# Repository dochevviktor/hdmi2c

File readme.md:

# HDMI2C Monitor Controller

HDMI2C allows network control (via WiFi) of monitors connected to it via HDMI (via
[DDC]). This allows you to build your own tooling and control systems for your monitors,
rather than relying on awkward inconvient buttons and OSDs. Think of it as an API for
your monitors.

This repository contains the hardware design, made with [KiCAD]. The current
**rev2 XIAO ESP32-C6 carrier is CAD-checked but not physically tested**. Its
[prototype package](hardware/rev2/README.md) includes the BOM, schematic, assembly
drawings, a detailed [3D assembly view](hardware/rev2/assembly-3d-front.png), STEP,
Gerbers, and drills. Open the current project with KiCad 10.

The staged plan for a single-monitor board, XIAO ESP32-C6 migration, and ESPHome
firmware is in [PLAN.md](PLAN.md), including progress and handoff notes for future
sessions. The [upstream BOM and schematic][pages] describe the original revision,
not the current carrier.

## What could you build with this

- A physical brightness knob
- Switch a monitor's input when you wake up your desktop PC or connect your laptop
  to your dock
- IDK probably some other weird shit

## Features

- Seeed Studio XIAO ESP32-C6 with Wi-Fi; soldered castellated mounting
- The XIAO's USB-C power, native programming/logging, regulator, and boot/reset
- One HDMI port (`J7`, HDMI1) with:
  - TPD12S016PWR-based 3.3 V/5 V DDC translation and buffered HPD input
  - Independently controlled DDC enable and protected HDMI 5 V output
- Two small top-actuated buttons and four back-side diagnostic pads
- 42 × 24 mm two-layer carrier with antenna cutout and copper keepouts

Rev2 has 12 fitted components, including the purchased XIAO module, and a 68%
smaller bounding-box area than the 70 × 45 mm single-port rev1. Connector overhangs
are outside those dimensions. There are no mounting holes; provide enclosure
support and cable strain relief.

See the [hardware notes and pin mapping](docs/stage2-hardware.md) for design
decisions, resource provenance, verification, and outstanding physical tests.
ERC/DRC and schematic/PCB parity are clean; 20 design/BOM/preview regression tests pass.
See the [JLCPCB preparation notes](docs/jlcpcb.md) before ordering: factory-specific
settings are applied and all 12 fitted part identities are matched, but final
assembly placement and assembler approval remain pending. J7 is the exact Würth
685119134923 HDMI socket, now matched to JLCPCB **C2930961**.
Historical rev1 findings are recorded in [stage-1 validation](docs/stage1-validation.md).

The updated [review workflow](docs/automation.md) validates rev2 and generates an
interactive BOM/schematic preview using KiCad 10. Pull requests cannot deploy to
Pages. The build was tested locally, including its pinned container; GitHub-hosted
execution and deployment have not been run here.

## JLCPCB submission files

The standard handoff is a ZIP of the [fabrication folder](hardware/rev2/fabrication/)
**including Gerbers, outline and drill files**, plus the clean
[BOM](hardware/rev2/bom-jlcpcb-draft.csv) and a finalized centroid/CPL placement file.
Use the same reviewed revision for all three. The user-managed `bom.csv` is a
matching report, not the clean upload BOM.

The [draft CPL](hardware/rev2/cpl-jlcpcb-draft.csv) puts the raw
[placement CSV](hardware/rev2/positions-front.csv) into JLCPCB's column format, but
U3/J7 still use footprint origins rather than centroids and all rotations are
unverified. Correct those in the online placement preview and confirm XIAO module
handling and soldering the HDMI shell tabs before ordering. See the
[submission checklist](docs/jlcpcb.md#files-to-submit).

## Firmware

Firmware is not included yet. [Stage 3 of the plan](PLAN.md#stage-3--esphome-firmware-over-wi-fi)
will add ESPHome firmware for Wi-Fi control of brightness and input selection,
targeting the XIAO ESP32-C6 carrier from stage 2.

## A word on monitor compatibility

Not all monitors implement DDC that well. Particularly of annoyance, some models I
tested would not listen to DDC commands on inputs that were not active, which, given
this project relies on you having a spare HDMI input which never carries any video, is
kind of a deal breaker.

### Known good monitors

- Dell U2515h — reported working by the original project's author with the
  original hardware/firmware; not yet retested with this XIAO/ESPHome redesign.

## Deferred ideas (outside the current plan)

- A larger carrier option with mounting holes
- Spare ESP32 IO broken out to headers for ease of hacking
- More ambitious, HDMI passthrough to allow use of the project without taking up a whole
  spare HDMI port.

## Is it that useful tho?

You can achieve the same thing without having to build your own hardware with a
Raspberry Pi 4. Support for dual monitor I2C (DDC) was added shortly before I started
this project - guess I didn't check enough :-). This is a much more accessible means to
achieve the same goal. However, if you want a more minimal solution that doesn't require
an entire embedded linux system, this project may be for you.

[DDC]: https://en.wikipedia.org/wiki/Display_Data_Channel
[KiCAD]: https://kicad.org
[pages]: https://wlcx.github.io/hdmi2c

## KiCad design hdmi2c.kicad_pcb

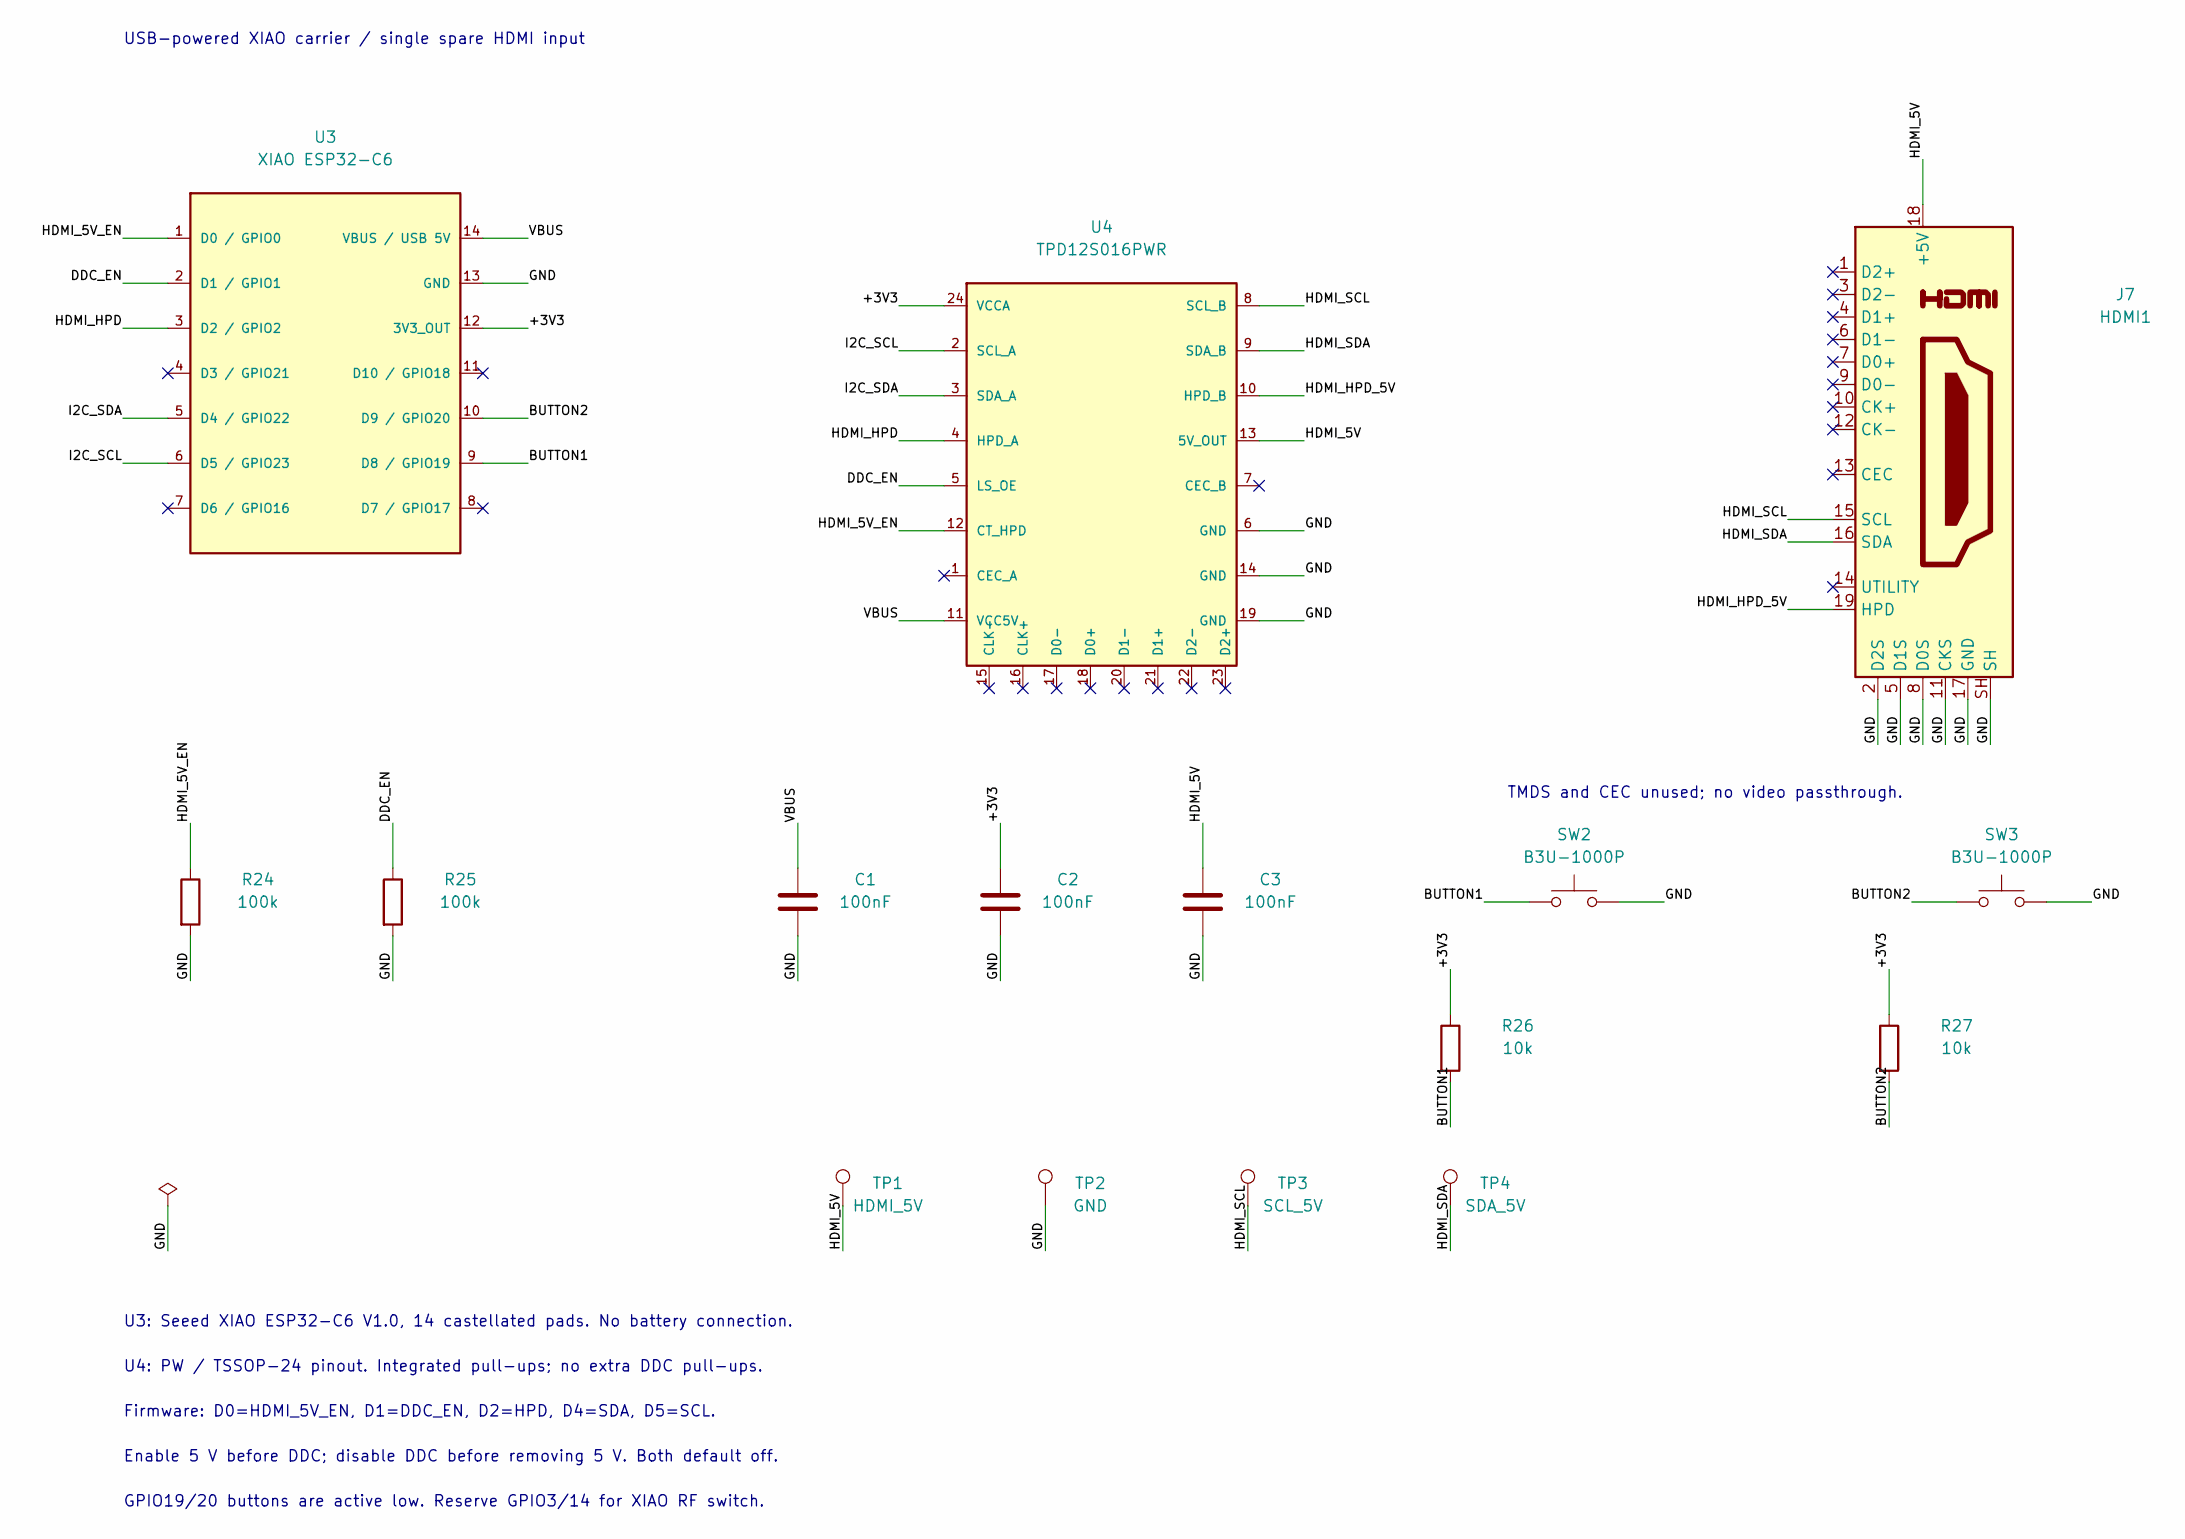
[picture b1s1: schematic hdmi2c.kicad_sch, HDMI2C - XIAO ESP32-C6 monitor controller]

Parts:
C1, C2, C3: 100nF; C_0603_1608Metric; MPN CC0603KRX7R9BB104; LCSC Part # C14663
J7: HDMI1; WURTH_685119134923_HDMI; MPN 685119134923; LCSC Part # C2930961
R24, R25: 100k; R_0603_1608Metric; MPN FRH0603B1003TS; LCSC Part # C51048211
R26, R27: 10k; R_0603_1608Metric; MPN SC0603F1002F2BNRH; LCSC Part # C3152123
SW2, SW3: B3U-1000P; SW_SPST_B3U-1000P; MPN B3U-1000P; LCSC Part # C231329
TP1: HDMI_5V; TestPoint_Pad_D1.0mm
TP2: GND; TestPoint_Pad_D1.0mm
TP3: SCL_5V; TestPoint_Pad_D1.0mm
TP4: SDA_5V; TestPoint_Pad_D1.0mm
U3: XIAO ESP32-C6; XIAO_ESP32C6_Castellated; MPN 113991254; LCSC Part # C27675191
U4: TPD12S016PWR; TSSOP-24_4.4x7.8mm_P0.65mm; MPN TPD12S016PWR; LCSC Part # C201665

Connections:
/+3V3: C2.1, R26.1, R27.1, U3.12 (3V3_OUT), U4.24 (VCCA)
/BUTTON1: R26.2, SW2.1, U3.9 (D8_/_GPIO19)
/BUTTON2: R27.2, SW3.1, U3.10 (D9_/_GPIO20)
/DDC_EN: R25.1, U3.2 (D1_/_GPIO1), U4.5 (LS_OE)
/GND: C1.2, C2.2, C3.2, J7.2 (D2S), J7.5 (D1S), J7.8 (D0S), J7.11 (CKS), J7.17 (GND), J7.SH, R24.2, R25.2, SW2.2, SW3.2, TP2.1 (1_1), U3.13 (GND), U4.6 (GND), U4.14 (GND), U4.19 (GND)
/HDMI_5V: C3.1, J7.18 (+5V), TP1.1 (1_1), U4.13 (5V_OUT)
/HDMI_5V_EN: R24.1, U3.1 (D0_/_GPIO0), U4.12 (CT_HPD)
/HDMI_HPD: U3.3 (D2_/_GPIO2), U4.4 (HPD_A)
/HDMI_HPD_5V: J7.19 (HPD), U4.10 (HPD_B)
/HDMI_SCL: J7.15 (SCL), TP3.1 (1_1), U4.8 (SCL_B)
/HDMI_SDA: J7.16 (SDA), TP4.1 (1_1), U4.9 (SDA_B)
/I2C_SCL: U3.6 (D5_/_GPIO23), U4.2 (SCL_A)
/I2C_SDA: U3.5 (D4_/_GPIO22), U4.3 (SDA_A)
/VBUS: C1.1, U3.14 (VBUS_/_USB_5V), U4.11 (VCC5V)

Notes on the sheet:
USB-powered XIAO carrier / single spare HDMI input
U3: Seeed XIAO ESP32-C6 V1.0, 14 castellated pads. No battery connection.
U4: PW / TSSOP-24 pinout. Integrated pull-ups; no extra DDC pull-ups.
Firmware: D0=HDMI_5V_EN, D1=DDC_EN, D2=HPD, D4=SDA, D5=SCL.
Enable 5 V before DDC; disable DDC before removing 5 V. Both default off.
GPIO19/20 buttons are active low. Reserve GPIO3/14 for XIAO RF switch.
TMDS and CEC unused; no video passthrough.

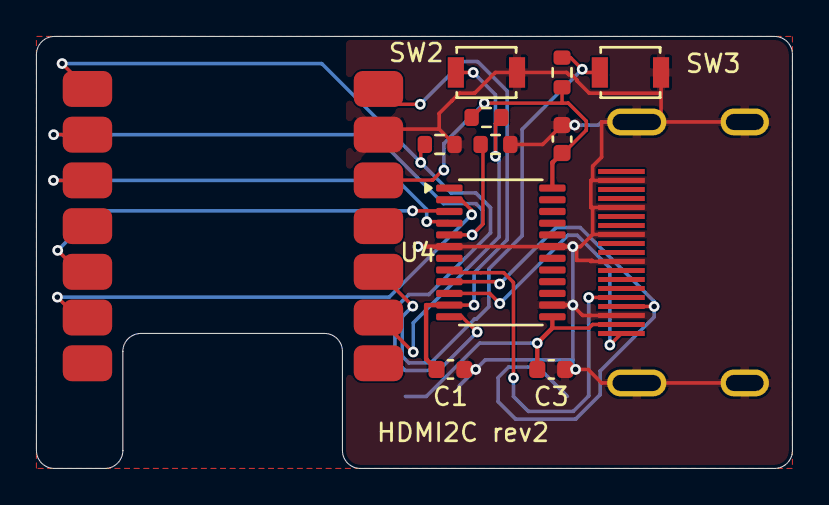
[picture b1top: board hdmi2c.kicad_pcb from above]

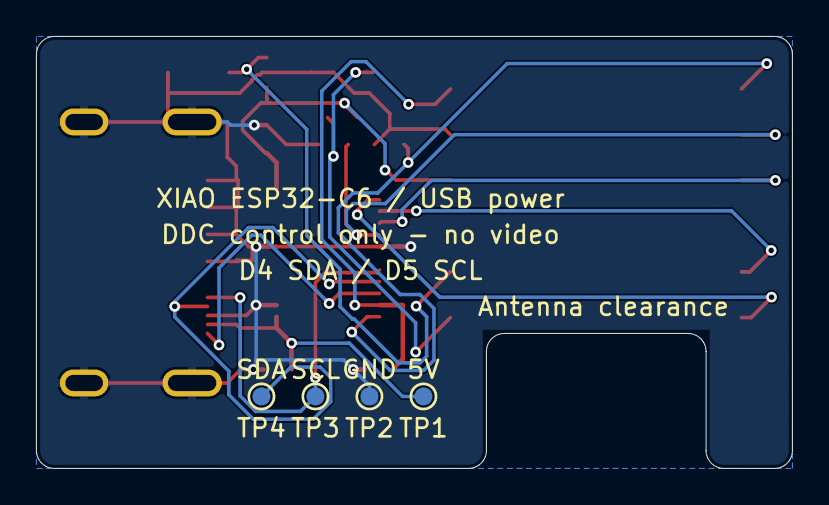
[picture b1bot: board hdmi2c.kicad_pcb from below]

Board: 2 copper layers, 42.0 x 24.0 mm, 16 parts (4 on the bottom side), 14 nets.

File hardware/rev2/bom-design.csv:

"References","Value","Footprint","Quantity","Manufacturer","MPN","LCSC Part #","Specification","Datasheet"
"C1-C3","100nF","Capacitor_SMD:C_0603_1608Metric","3","YAGEO","CC0603KRX7R9BB104","C14663","100 nF; >=16 V; X7R; +/-10%; 0603",""
"J7","HDMI1","hdmi2c:WURTH_685119134923_HDMI","1","Wurth Elektronik","685119134923","C2930961","HDMI Type A receptacle; SMT contacts and plated-slot shell tabs","https://www.we-online.com/components/products/datasheet/6851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"
"R24,R25","100k","Resistor_SMD:R_0603_1608Metric","2","FOJAN","FRH0603B1003TS","C51048211","100 kohm; >=0.1 W; +/-1%; 0603",""
"R26,R27","10k","Resistor_SMD:R_0603_1608Metric","2","Sunway","SC0603F1002F2BNRH","C3152123","10 kohm; >=0.1 W; +/-1%; 0603",""
"SW2,SW3","B3U-1000P","Button_Switch_SMD:SW_SPST_B3U-1000P","2","Omron","B3U-1000P","C231329","Top-actuated SPST-NO; no locating boss","https://omronfs.omron.com/en_US/ecb/products/pdf/en-b3u.pdf"
"U3","XIAO ESP32-C6","hdmi2c:XIAO_ESP32C6_Castellated","1","Seeed Studio","113991254","C27675191","Complete V1.0 module; 14 soldered castellations; 4 MB flash","https://files.seeedstudio.com/wiki/SeeedStudio-XIAO-ESP32C6/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"
"U4","TPD12S016PWR","Package_SO:TSSOP-24_4.4x7.8mm_P0.65mm","1","Texas Instruments","TPD12S016PWR","C201665","PW/TSSOP-24; do not substitute the RKT pinout","https://www.ti.com/lit/ds/symlink/tpd12s016.pdf"
